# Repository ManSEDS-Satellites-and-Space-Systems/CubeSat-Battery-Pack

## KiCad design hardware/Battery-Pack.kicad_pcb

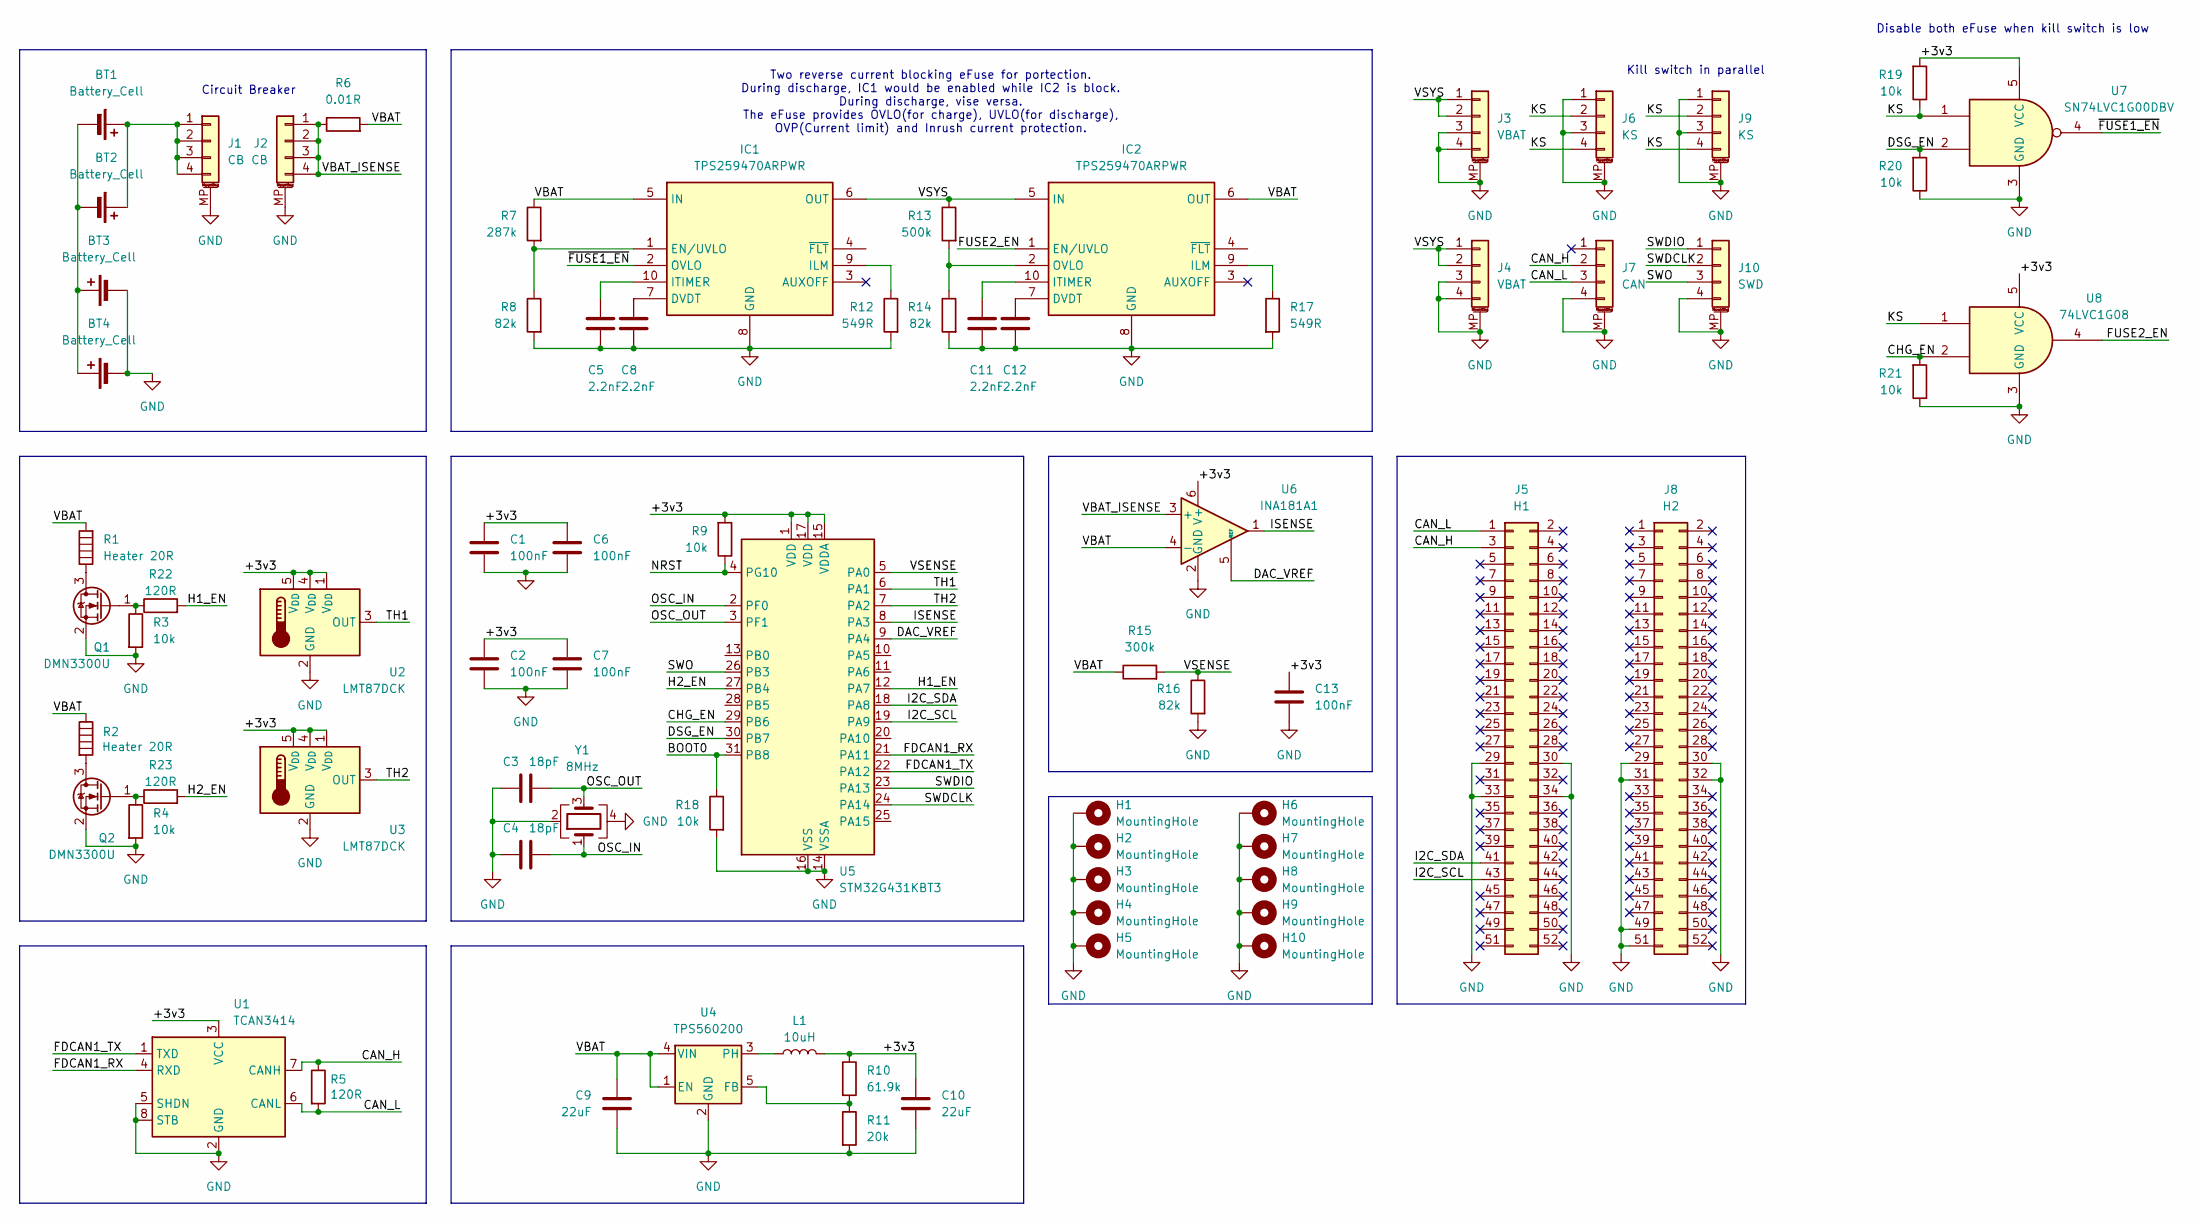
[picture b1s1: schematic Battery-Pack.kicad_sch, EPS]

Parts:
BT1, BT2, BT3, BT4: Battery_Cell; 18650-THT
C1, C2, C6, C7, C13: 100nF; C_0603_1608Metric; Mouser Part Number 603-C0603JRX7R7BB104
C3, C4: 18pF; C_0603_1608Metric; Mouser Part Number 603-CC603FRNPO9BN180
C5, C8, C11, C12: 2.2nF; C_0603_1608Metric; Mouser Part Number 603-C0603JRX7R7BB104
C9, C10: 22uF; C_0603_1608Metric; Mouser Part Number 603-C0603JRX7R7BB104
H1, H2, H3, H4, H5, H10: MountingHole; MountingHole_2.7mm_M2.5_DIN965_Pad
H6, H7, H8, H9: MountingHole; MountingHole_3.2mm_M3_DIN965_Pad
IC1, IC2: TPS259470ARPWR; Mouser Part Number 595-TPS259470ARPWR
J1, J2: CB; Molex_Pico-Lock_504050-0491_1x04-1MP_P1.50mm_Horizontal; Mouser Part Number 538-504050-0491
J3, J4: VBAT; Molex_Pico-Lock_504050-0491_1x04-1MP_P1.50mm_Horizontal; Mouser Part Number 538-504050-0491
J5: H1; PinHeader_2x26_P2.54mm_Vertical
J6, J9: KS; Molex_Pico-Lock_504050-0491_1x04-1MP_P1.50mm_Horizontal; Mouser Part Number 538-504050-0491
J7: CAN; Molex_Pico-Lock_504050-0491_1x04-1MP_P1.50mm_Horizontal; Mouser Part Number 538-504050-0491
J8: H2; PinHeader_2x26_P2.54mm_Vertical
J10: SWD; Molex_Pico-Lock_504050-0491_1x04-1MP_P1.50mm_Horizontal; Mouser Part Number 538-504050-0491
L1: 10uH; L_APV_APH0618
Q1, Q2: DMN3300U; SOT-23; Mouser Part Number 621-DMN3300U-7
R1, R2: Heater 20R; R_Axial_DIN0617_L17.0mm_D6.0mm_P30.48mm_Horizontal; Mouser Part Number 279-4-2176793-0
R3, R4, R9, R18, R19, R20, R21: 10k; R_0603_1608Metric; Mouser Part Number 603-AC0603DR-0710KL
R5: 120R; R_0603_1608Metric; Mouser Part Number 603-AC0603FR-07120RL; LCSC C118142
R6: 0.01R; R_0805_2012Metric
R7: 287k; R_0603_1608Metric; Mouser Part Number 603-AC0603DR-0710KL
R8, R14, R16: 82k; R_0603_1608Metric; Mouser Part Number 603-AC0603DR-0710KL
R10: 61.9k; R_0603_1608Metric; Mouser Part Number 603-AC0603DR-0710KL
R11: 20k; R_0603_1608Metric; Mouser Part Number 603-AC0603DR-0710KL
R12, R17: 549R; R_0603_1608Metric; Mouser Part Number 603-AC0603DR-0710KL
R13: 500k; R_0603_1608Metric; Mouser Part Number 603-AC0603DR-0710KL
R15: 300k; R_0603_1608Metric
R22, R23: 120R; R_0603_1608Metric
U1: TCAN3414; SOIC-8_3.9x4.9mm_P1.27mm; Mouser Part Number 595-TCAN3414DRBR
U2, U3: LMT87DCK; SOT-353_SC-70-5
U4: TPS560200; SOT-23-5
U5: STM32G431KBT3; LQFP-32_7x7mm_P0.8mm; Mouser Part Number 511-STM32G431KBT3
U6: INA181A1; SOT-23-6
U7: SN74LVC1G00DBV; SOT-23-5
U8: 74LVC1G08; SOT-23-5
Y1: 8MHz; Crystal_SMD_3225-4Pin_3.2x2.5mm; Mouser Part Number 815-M8AIG-8-1ZT

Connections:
/+3v3: C1.1, C2.1, C6.1, C7.1, C10.1, C13.1, L1.2, R9.2, R10.1, R19.2, U1.3 (VCC), U2.1 (V_{DD}), U2.4 (V_{DD}), U2.5 (V_{DD}), U3.1 (V_{DD}), U3.4 (V_{DD}), U3.5 (V_{DD}), U5.1 (VDD), U5.15 (VDDA), U5.17 (VDD), U6.6 (V+), U7.5 (VCC), U8.5 (VCC)
/BOOT0: R18.1, U5.31 (PB8)
/CAN_H: J5.3, J7.2, R5.1, U1.7 (CANH)
/CAN_L: J5.1, J7.3, R5.2, U1.6 (CANL)
/CHG_EN: R21.2, U5.29 (PB6), U8.2
/DAC_VREF: U5.9 (PA4), U6.5 (REF)
/DSG_EN: R20.2, U5.30 (PB7), U7.2
/FDCAN1_RX: U1.4 (RXD), U5.21 (PA11)
/FDCAN1_TX: U1.1 (TXD), U5.22 (PA12)
/FUSE2_EN: IC2.1 (EN/UVLO), IC2.11 (EN/UVLO), U8.4
/H1_EN: R22.2, U5.12 (PA7)
/H2_EN: R23.2, U5.27 (PB4)
/I2C_SCL: J5.43, U5.19 (PA9)
/I2C_SDA: J5.41, U5.18 (PA8)
/ISENSE: U5.8 (PA3), U6.1
/KS: J6.2, J6.4, J9.2, J9.4, R19.1, U7.1, U8.1
/NRST: R9.1, U5.4 (PG10)
/OSC_IN: C4.2, U5.2 (PF0), Y1.1
/OSC_OUT: C3.2, U5.3 (PF1), Y1.3
/SWDCLK: J10.2, U5.24 (PA14)
/SWDIO: J10.1, U5.23 (PA13)
/SWO: J10.3, U5.26 (PB3)
/TH1: U2.3 (OUT), U5.6 (PA1)
/TH2: U3.3 (OUT), U5.7 (PA2)
/VBAT: C9.1, IC1.5 (IN), IC2.6 (OUT), R1.2, R2.1, R6.2, R7.1, R15.1, U4.1 (EN), U4.4 (VIN), U6.4 (-)
/VBAT_ISENSE: J2.1, J2.2, J2.3, J2.4, R6.1, U6.3 (+)
/VSENSE: R15.2, R16.1, U5.5 (PA0)
/VSYS: IC1.6 (OUT), IC2.5 (IN), J3.1, J3.2, J4.1, J4.2, R13.1
/~FUSE1_EN: IC1.2 (OVLO), U7.4
GND: BT3.2 (-), BT4.2 (-), C1.2, C2.2, C3.1, C4.1, C5.2, C6.2, C7.2, C8.2, C9.2, C10.2, C11.2, C12.2, C13.2, H1.1, H2.1, H3.1, H4.1, H5.1, H6.1, H7.1, H8.1, H9.1, H10.1, IC1.8 (GND), IC2.8 (GND), J1.MP (MountPin), J2.MP (MountPin), J3.3, J3.4, J3.MP (MountPin), J4.3, J4.4, J4.MP (MountPin), J5.29, J5.30, J5.33, J5.34, J6.1, J6.3, J6.MP (MountPin), J7.4, J7.MP (MountPin), J8.29, J8.30, J8.31, J8.32, J8.49, J8.51, J9.1, J9.3, J9.MP (MountPin), J10.4, J10.MP (MountPin), Q1.2 (S), Q2.2 (S), R3.2, R4.2, R8.2, R11.2, R12.2, R14.2, R16.2, R17.2, R18.2, R20.1, R21.1, U1.2 (GND), U1.5 (SHDN), U1.8 (STB), U2.2 (GND), U3.2 (GND), U4.2 (GND), U5.14 (VSSA), U5.16 (VSS), U5.32 (VSS), U6.2 (GND), U7.3 (GND), U8.3 (GND), Y1.2, Y1.4
unnamed: BT1.1 (+), BT2.1 (+), J1.1, J1.2, J1.3, J1.4
unnamed: BT1.2 (-), BT2.2 (-), BT3.1 (+), BT4.1 (+)
unnamed: C5.1, IC1.10 (ITIMER), IC1.14 (ITIMER)
unnamed: C8.1, IC1.7 (DVDT), IC1.13 (DVDT)
unnamed: C11.1, IC2.10 (ITIMER), IC2.14 (ITIMER)
unnamed: C12.1, IC2.7 (DVDT), IC2.13 (DVDT)
unnamed: IC1.1 (EN/UVLO), IC1.11 (EN/UVLO), R7.2, R8.1
unnamed: IC1.9 (ILM), R12.1
unnamed: IC1.4 (~FLT), IC1.12 (~FLT)
unnamed: IC2.9 (ILM), R17.1
unnamed: IC2.2 (OVLO), R13.2, R14.1
unnamed: IC2.4 (~FLT), IC2.12 (~FLT)
unnamed: Q1.3 (D), R1.1
unnamed: Q1.1 (G), R3.1, R22.1
unnamed: Q2.3 (D), R2.2
unnamed: Q2.1 (G), R4.1, R23.1
unnamed: R10.2, R11.1, U4.5 (FB)
unnamed: L1.1, U4.3 (PH)

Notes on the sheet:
Circuit Breaker
Disable both eFuse when kill switch is low
Two reverse current blocking eFuse for portection. During discharge, IC1 would be enabled while IC2 is block. During discharge, vise versa. The eFuse provides OVLO(for charge), UVLO(for discharge), OVP(Current limit) and Inrush current protection.
Kill switch in parallel

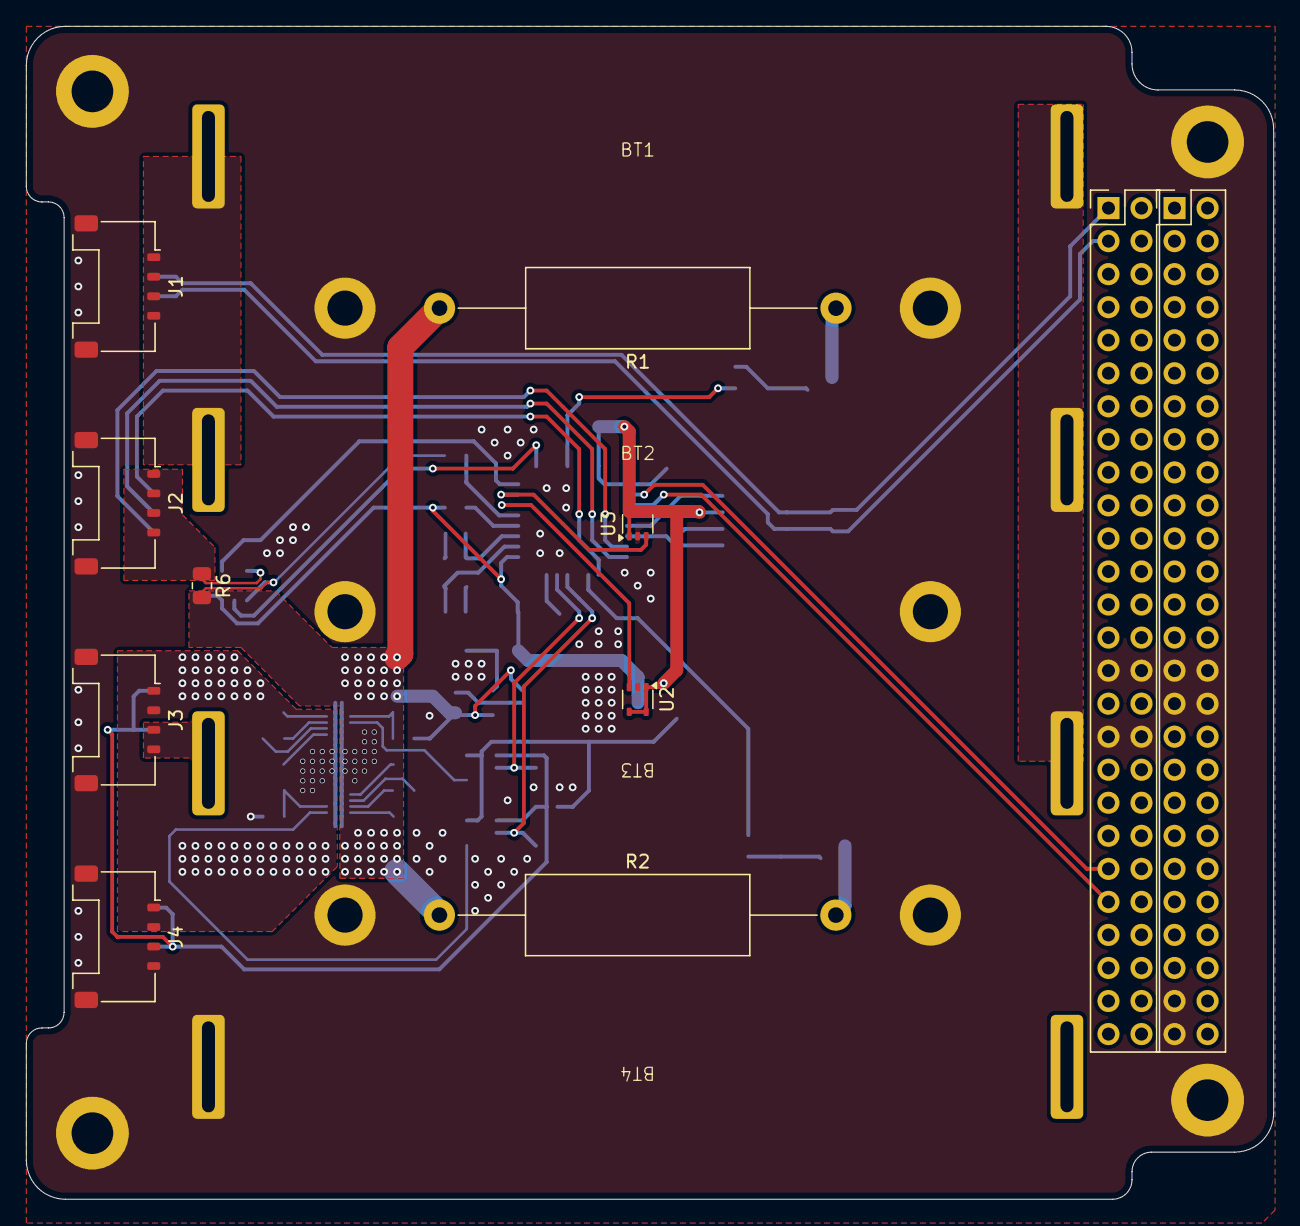
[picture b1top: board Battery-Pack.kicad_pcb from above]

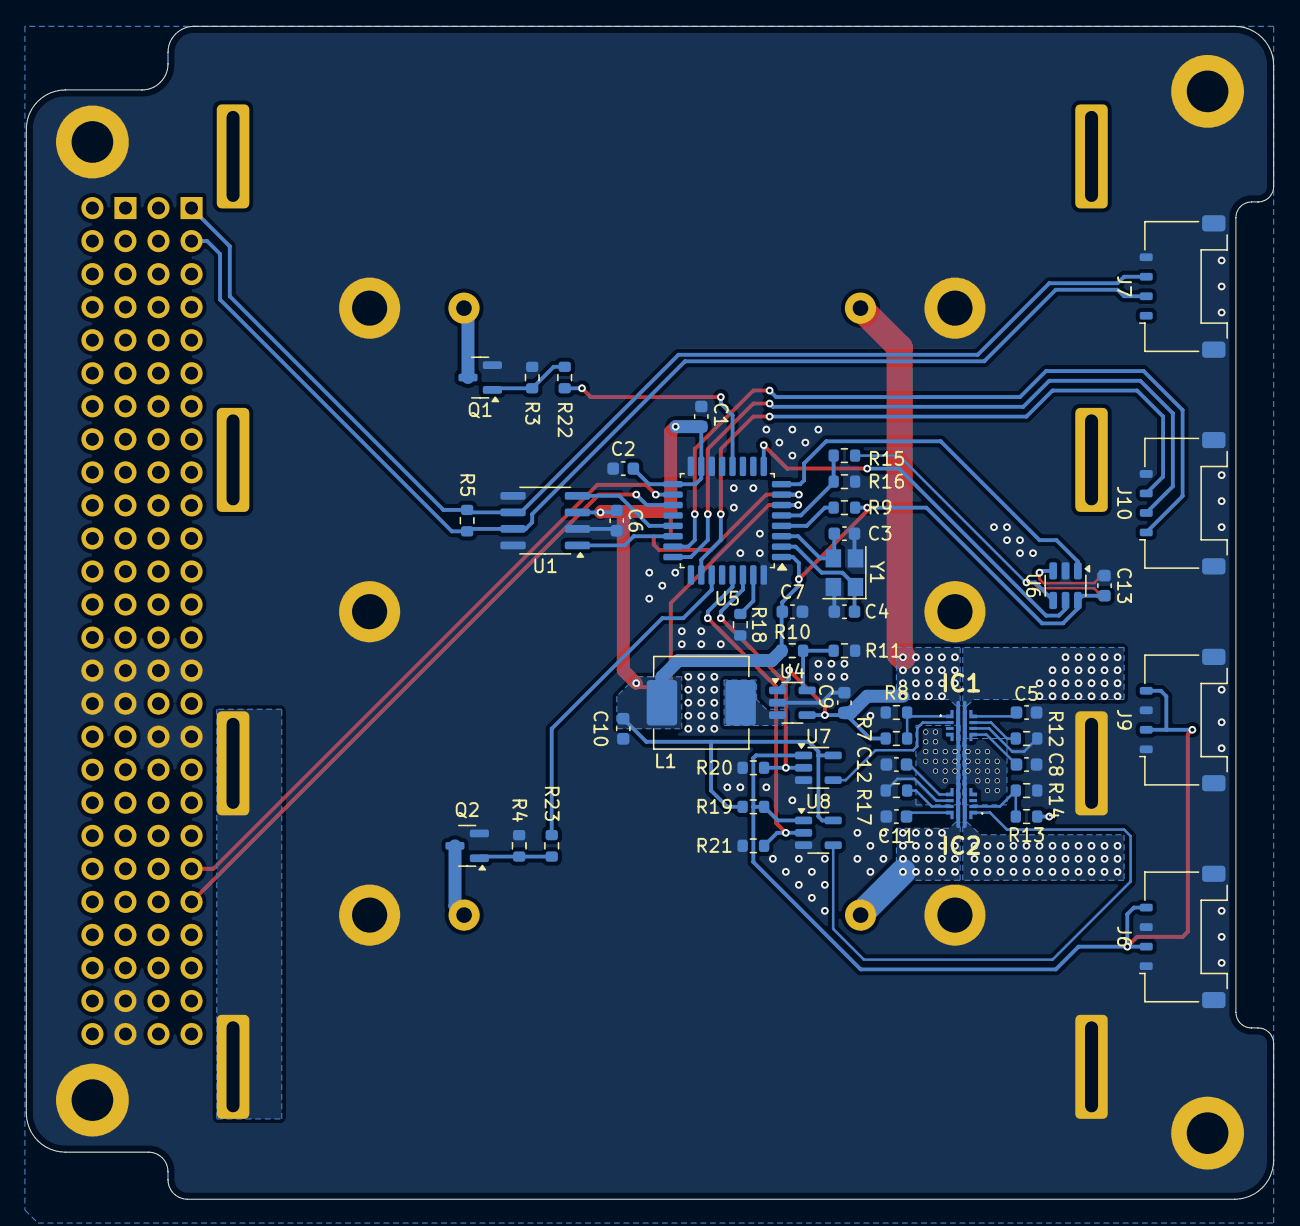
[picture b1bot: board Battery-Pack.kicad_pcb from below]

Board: 2 copper layers, 95.9 x 90.2 mm, 74 parts (49 on the bottom side), 48 nets.
